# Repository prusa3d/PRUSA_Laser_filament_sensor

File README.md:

# PRUSA Laser filament sensor

Filament presence and velocity detection using a [PAT9125EL optical laser movement sensor](http://www.pixart.com.tw/product_data.asp?product_id=173&productclassify_id=18&productclassify2_id=51&productclassify_name=Optical%20Tracking%20Sensors&productclassify2_name=Consumer&partnumber=PAT9125EL-TKIT%20PAT9125EL-TKMT), operating at 850nm.

See also:
* [PAT9125EL datasheet](http://www.pixart.com/upload/PAT9125EL_GDS_V1.2_31052017_20171011150843.pdf)
* [boucaron's investigation into this board](https://steemit.com/printing3d/@boucaron/prusa-mk3-filament-detector-short-study)

# KiCad PCB layout

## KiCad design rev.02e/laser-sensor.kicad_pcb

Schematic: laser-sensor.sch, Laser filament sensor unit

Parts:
C1, C4: 4u7; C_0603
C2: 10u; C_0603
C3: 100n; C_0603
F1: 50mA; R_1206
P1: CONN_01X04; Pin_Header_Angled_1x04
R1, R2: 4k7; R_0603
R3: 200k; R_0603
U1: PAT9125EL
U2: MCP1703T-3302E/CB; SOT-23
U3: LSF0102

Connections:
GND: C1.2, C2.2, C3.2, C4.2, P1.2, U1.4, U1.8, U2.1 (GND), U3.1
unnamed: C1.1, U1.2
unnamed: C2.1, C3.1, U1.1, U1.3, U2.2 (OUT), U3.2
unnamed: C4.1, F1.2, R1.2, R2.1, R3.2, U2.3 (IN)
unnamed: F1.1, P1.1
unnamed: P1.3, R1.1, U3.6
unnamed: P1.4, R2.2, U3.5
unnamed: R3.1, U3.7, U3.8
unnamed: U1.5, U3.3
unnamed: U1.6, U3.4

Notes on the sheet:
+5V GND SCL SDA

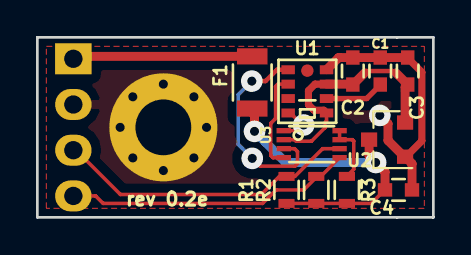
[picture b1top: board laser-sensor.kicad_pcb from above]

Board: 2 copper layers, 22.0 x 10.0 mm, 12 parts (1 on the bottom side), 10 nets.

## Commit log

2017-12-01 rev.02
2018-05-14 rev_0.2e
2018-06-22 add basic info to the README
    Hopefully it'll save others some time researching this.
